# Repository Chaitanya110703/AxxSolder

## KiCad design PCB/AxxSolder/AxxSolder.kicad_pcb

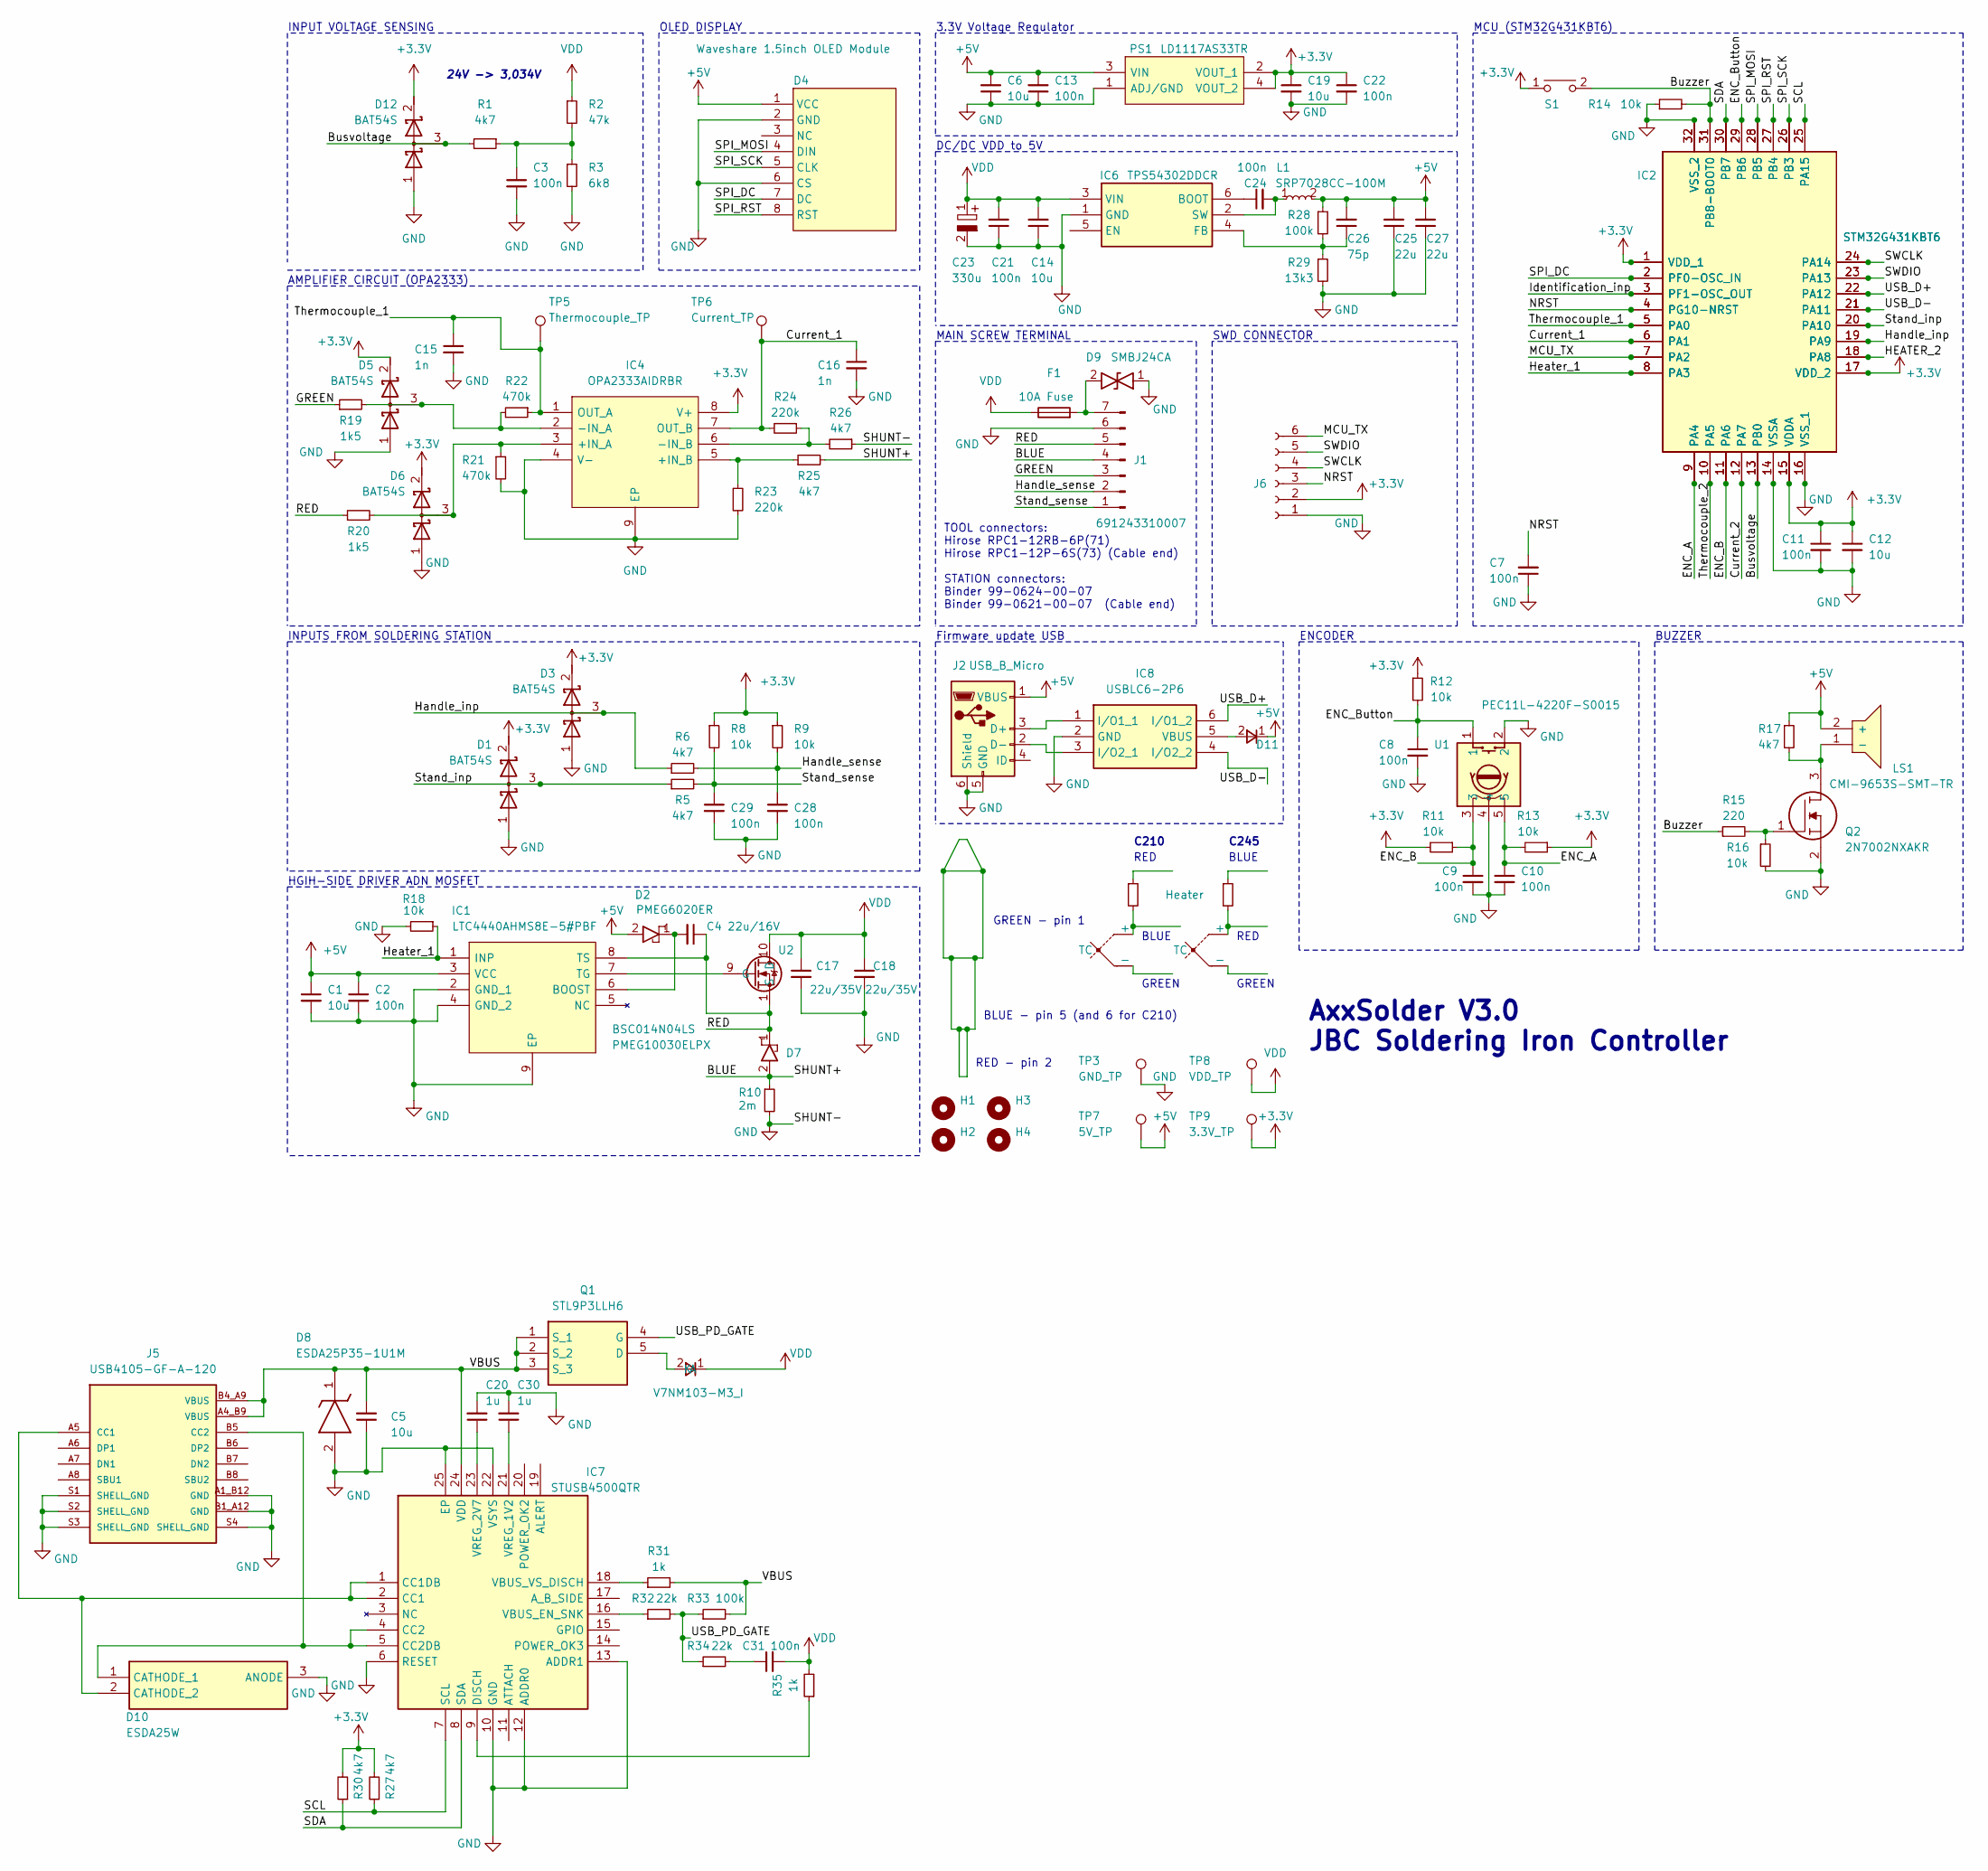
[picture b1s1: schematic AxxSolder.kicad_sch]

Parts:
C1, C5, C6, C12, C14, C19: 10u; C_0805_2012Metric
C2, C3, C7, C8, C9, C10, C11, C13, C21, C22, C24, C28, C29, C31: 100n; C_0805_2012Metric
C4: 22u/16V; C_1206_3216Metric
C15, C16: 1n; C_0805_2012Metric
C17, C18: 22u/35V; C_1206_3216Metric
C20, C30: 1u; C_0805_2012Metric
C23: 330u; CAPAE1030X1050N; Mouser Part Number 661-EMZR500ARA331MJA
C25, C27: 22u; C_1206_3216Metric
C26: 75p; C_0805_2012Metric
D1, D3, D5, D6, D12: BAT54S; SOT95P230X110-3N
D2: PMEG6020ER; PMEG6020ER115; Mouser Part Number 771-PMEG6020ER-115
D4: Waveshare 1.5inch OLED Module; 1_5inch-rgb-oled-module_asm-1110
D7: PMEG10030ELPX; SODFL4725X110N; Mouser Part Number 771-PMEG10030ELPX
D8: ESDA25P35-1U1M; ESDA25P351U1M; Mouser Part Number 511-ESDA25P35-1U1M
D9: SMBJ24CA; DIOM5436X261N; Mouser Part Number 576-SMBJ24CA
D10: ESDA25W; SOT65P210X110-3N; Mouser Part Number 511-ESDA25W
D11: 1N5819HW-7-F; SOD3716X145N; Mouser Part Number 621-1N5819HW-F
D13: V7NM103-M3_I; V7NM103M3I; Mouser Part Number 625-V7NM103-M3/I
F1: 10A Fuse; 3557-2
H1, H2, H3, H4: MountingHole; MountingHole_3mm
IC1: LTC4440AHMS8E-5#PBF; SOP65P490X110-9N; Mouser Part Number 584-C4440AHMS8E-5PBF
IC2: STM32G431KBT6; QFP80P900X900X160-32N; Mouser Part Number 511-STM32G431KBT6
IC4: OPA2333AIDRBR; SON65P300X300X100-9N-D; Mouser Part Number 595-OPA2333AIDRBR
IC5: STM32G431KBT6; UFQFPN-32-1EP_5x5mm_P0.5mm_EP3.5x3.5mm; Mouser Part Number 511-STM32G431KBT6
IC6: TPS54302DDCR; SOT95P280X110-6N; Mouser Part Number 595-TPS54302DDCR
IC7: STUSB4500QTR; QFN50P400X400X100-25N-D; Mouser Part Number 511-STUSB4500QTR
IC8: USBLC6-2P6; USBLC62P6; Mouser Part Number 511-USBLC6-2P6
J1: Conn_01x07_Male; 691243310007; Manufacturer_Part_Number 691243310007
J2: USB_B_Micro; GCT_USB3140-30-0230-1-C_REVE1
J5: USB4105-GF-A-120; GCT_USB4105-GF-A-120; PARTREV A3
J6: Conn_01x06_Socket; PinSocket_1x06_P2.54mm_Vertical
L1: SRP7028CC-100M; INDPM7366X300N; Manufacturer_Part_Number SRP7028CC-100M
LS1: CMI-9653S-SMT-TR; CMI9653SSMTTR; Mouser Part Number 490-CMI-9653S-SMT-TR
PS1: LD1117AS33TR; SOT230P700X190-4N; Mouser Part Number 511-LD1117AS33
Q1: STL9P3LLH6; STL20N6F7; Mouser Part Number 511-STL9P3LLH6
Q2: 2N7002NXAKR; SOT95P230X110-3N; Manufacturer_Part_Number 2N7002NXAKR; Mouser Part Number 771-2N7002NXAKR
R1, R5, R6, R17, R25, R26, R27, R30: 4k7; R_0805_2012Metric
R2: 47k; R_0805_2012Metric
R3: 6k8; R_0805_2012Metric
R4: Heater
R7: Heater 2 OHM
R8, R9, R11, R12, R13, R14, R16, R18: 10k; R_0805_2012Metric
R10: 2m; RESC6432X89N; part_id WSLP25122L500FEA
R15: 220; R_0805_2012Metric
R19, R20: 1k5; R_0805_2012Metric
R21, R22: 470k; R_0805_2012Metric
R23, R24: 220k; R_0805_2012Metric
R28, R33: 100k; R_0805_2012Metric
R29: 13k3; R_0805_2012Metric
R31, R35: 1k; R_0805_2012Metric
R32, R34: 22k; R_0805_2012Metric
S1: PTS636_SM43_SMTR_LFS; PTS636SM43SMTRLFS; Mouser Part Number 611-PTS636SM43SMTRLF
TC1, TC2: TC
TP3: GND_TP; TestPoint_THTPad_D1.0mm_Drill0.5mm
TP5: Thermocouple_TP; TestPoint_Pad_D1.0mm
TP6: Current_TP; TestPoint_Pad_D1.0mm
TP7: 5V_TP; TestPoint_THTPad_D1.0mm_Drill0.5mm
TP8: VDD_TP; TestPoint_THTPad_D1.0mm_Drill0.5mm
TP9: 3.3V_TP; TestPoint_THTPad_D1.0mm_Drill0.5mm
U1: PEC11L-4220F-S0015; PEC11L4220FS0015; Mouser Part Number 652-PEC11L4220FS0015
U2: BSC014N04LS

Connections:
+3.3V: C11.1, C12.1, C19.1, C22.1, D1.2 (K), D3.2 (K), D5.2 (K), D6.2 (K), D12.2 (K), IC2.1 (VDD_1), IC2.15 (VDDA), IC2.17 (VDD_2), IC4.8 (V+), IC5.1 (VDD_1), IC5.15 (VDDA), IC5.17 (VDD_2), J6.2, PS1.2 (VOUT_1), PS1.4 (VOUT_2), R8.1, R9.1, R11.2, R12.1, R13.1, R27.2, R30.2, S1.1, TP9.1
+5V: C1.1, C2.1, C6.2, C13.2, C25.2, C26.2, C27.2, D2.2, D4.1 (VCC), D11.1, IC1.3 (VCC), J2.1 (VBUS), L1.2, LS1.2 (+), PS1.3 (VIN), R17.1, R28.1, TP7.1
/BLUE: D7.2, J1.4, R10.1, R25.2
/Busvoltage: D12.3 (common), IC2.13 (PB0), IC5.13 (PB0), R1.2
/Buzzer: IC2.31 (PB8-BOOT0), IC5.31 (PB8-BOOT0), R14.2, R15.1, S1.2
/Current_1: C16.1, IC2.6 (PA1), IC4.7 (OUT_B), IC5.6 (PA1), R24.2, TP6.1
/Current_2: IC2.12 (PA7), IC5.12 (PA7)
/ENC_A: C10.1, IC2.9 (PA4), IC5.9 (PA4), R13.2, U1.5
/ENC_B: C9.1, IC2.11 (PA6), IC5.11 (PA6), R11.1, U1.3
/ENC_Button: C8.1, IC2.29 (PB6), IC5.29 (PB6), R12.2, U1.1
/GREEN: J1.3, R19.1
/HEATER_2: IC2.18 (PA8), IC5.18 (PA8)
/Handle_inp: D3.3 (common), IC2.19 (PA9), IC5.19 (PA9), R6.1
/Handle_sense: C28.1, J1.2, R6.2, R9.2
/Heater_1: IC1.1 (INP), IC2.8 (PA3), IC5.8 (PA3), R18.1
/Identification_inp: IC2.3 (PF1-OSC_OUT), IC5.3 (PF1-OSC_OUT)
/MCU_TX: IC2.7 (PA2), IC5.7 (PA2), J6.6
/NRST: C7.2, IC2.4 (PG10-NRST), IC5.4 (PG10-NRST), J6.3
/RED: C4.1, D7.1, IC1.8 (TS), J1.5, R20.1, U2.1 (S)
/SCL: IC2.25 (PA15), IC5.25 (PA15), IC7.7 (SCL), R27.1
/SDA: IC2.30 (PB7), IC5.30 (PB7), IC7.8 (SDA), R30.1
/SPI_DC: D4.7 (DC), IC2.2 (PF0-OSC_IN), IC5.2 (PF0-OSC_IN)
/SPI_MOSI: D4.4 (DIN), IC2.28 (PB5), IC5.28 (PB5)
/SPI_RST: D4.8 (RST), IC2.27 (PB4), IC5.27 (PB4)
/SPI_SCK: D4.5 (CLK), IC2.26 (PB3), IC5.26 (PB3)
/SWCLK: IC2.24 (PA14), IC5.24 (PA14), J6.4
/SWDIO: IC2.23 (PA13), IC5.23 (PA13), J6.5
/Stand_inp: D1.3 (common), IC2.20 (PA10), IC5.20 (PA10), R5.1
/Stand_sense: C29.1, J1.1, R5.2, R8.2
/Thermocouple_1: C15.1, IC2.5 (PA0), IC4.1 (OUT_A), IC5.5 (PA0), R22.1, TP5.1
/Thermocouple_2: IC2.10 (PA5), IC5.10 (PA5)
/USB_D+: IC2.22 (PA12), IC5.22 (PA12), IC8.6 (I/O1_2)
/USB_D-: IC2.21 (PA11), IC5.21 (PA11), IC8.4 (I/O2_2)
/USB_PD_GATE: Q1.4 (G), R32.2, R33.1, R34.1
/VBUS: C5.2, D8.1 (K), IC7.24 (VDD), J5.A4_B9 (VBUS), J5.B4_A9 (VBUS), Q1.1 (S_1), Q1.2 (S_2), Q1.3 (S_3), R31.2, R33.2
GND: C1.2, C2.2, C3.2, C5.1, C6.1, C7.1, C8.2, C9.2, C10.2, C11.2, C12.2, C13.1, C14.1, C15.2, C16.2, C17.2, C18.2, C19.2, C20.2, C21.1, C22.2, C23.2, C25.1, C27.1, C28.2, C29.2, C30.2, D1.1 (A), D3.1 (A), D4.2 (GND), D4.6 (CS), D5.1 (A), D6.1 (A), D8.2 (A), D9.1, D10.3 (ANODE), D12.1 (A), IC1.2 (GND_1), IC1.4 (GND_2), IC1.9 (EP), IC2.14 (VSSA), IC2.16 (VSS_1), IC2.32 (VSS_2), IC4.4 (V-), IC4.9 (EP), IC5.14 (VSSA), IC5.16 (VSS_1), IC5.32 (VSS_2), IC6.1 (GND), IC7.6 (RESET), IC7.10 (GND), IC7.12 (ADDR0), IC7.13 (ADDR1), IC7.22 (VSYS), IC7.25 (EP), IC8.2 (GND), J1.6, J2.5 (GND), J2.6 (Shield), J5.A1_B12 (GND), J5.B1_A12 (GND), J5.S1 (SHELL_GND), J5.S2 (SHELL_GND), J5.S3 (SHELL_GND), J5.S4 (SHELL_GND), J6.1, PS1.1 (ADJ/GND), Q2.2, R3.2, R10.2, R14.1, R16.2, R18.2, R21.2, R23.2, R26.1, R29.2, TP3.1, U1.2, U1.4
unnamed: C3.1, R1.1, R2.2, R3.1
unnamed: C31.1, R34.2
unnamed: D5.3 (common), IC4.2 (-IN_A), R19.2, R22.2
unnamed: D6.3 (common), IC4.3 (+IN_A), R20.2, R21.1
unnamed: D10.1 (CATHODE_1), IC7.4 (CC2), IC7.5 (CC2DB), J5.B5 (CC2)
unnamed: D10.2 (CATHODE_2), IC7.1 (CC1DB), IC7.2 (CC1), J5.A5 (CC1)
unnamed: D13.2 (A), Q1.5 (D)
unnamed: C4.2, D2.1, IC1.6 (BOOST)
unnamed: IC1.7 (TG), U2.9 (G)
unnamed: IC4.5 (+IN_B), R23.1, R25.1
unnamed: IC4.6 (-IN_B), R24.1, R26.2
unnamed: C24.1, IC6.6 (BOOT)
unnamed: C26.1, IC6.4 (FB), R28.2, R29.1
unnamed: C24.2, IC6.2 (SW), L1.1
unnamed: IC7.9 (DISCH), R35.1
unnamed: IC7.16 (VBUS_EN_SNK), R32.1
unnamed: IC7.18 (VBUS_VS_DISCH), R31.1
unnamed: C30.1, IC7.21 (VREG_1V2)
unnamed: C20.1, IC7.23 (VREG_2V7)
unnamed: IC8.1 (I/O1_1), J2.3 (D+)
unnamed: IC8.3 (I/O2_1), J2.2 (D-)
unnamed: D11.2, IC8.5 (VBUS)
unnamed: D9.2, F1.2, J1.7
unnamed: LS1.1 (-), Q2.3, R17.2
unnamed: Q2.1, R15.2, R16.1
unnamed: R4.2, TC1.1 (+)
unnamed: R7.2, TC2.1 (+)
VDD: C14.2, C17.1, C18.1, C21.2, C23.1, C31.2, D13.1 (K), F1.1, IC6.3 (VIN), R2.1, R35.2, TP8.1, U2.10 (D)

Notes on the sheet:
C210
Firmware update USB
MCU (STM32G431KBT6)
C245
GREEN - pin 1
MAIN SCREW TERMINAL
AMPLIFIER CIRCUIT (OPA2333)
24V -> 3,034V
INPUT VOLTAGE SENSING
ENCODER
SWD CONNECTOR
BLUE
BLUE - pin 5 (and 6 for C210)
GREEN
RED
BUZZER
DC/DC VDD to 5V
AxxSolder V3.0 JBC Soldering Iron Controller
TOOL connectors: Hirose RPC1-12RB-6P(71) Hirose RPC1-12P-6S(73) (Cable end) STATION connectors: Binder 99-0624-00-07 Binder 99-0621-00-07 (Cable end)
INPUTS FROM SOLDERING STATION
HGIH-SIDE DRIVER ADN MOSFET
RED - pin 2
RED
3.3V Voltage Regulator
OLED DISPLAY

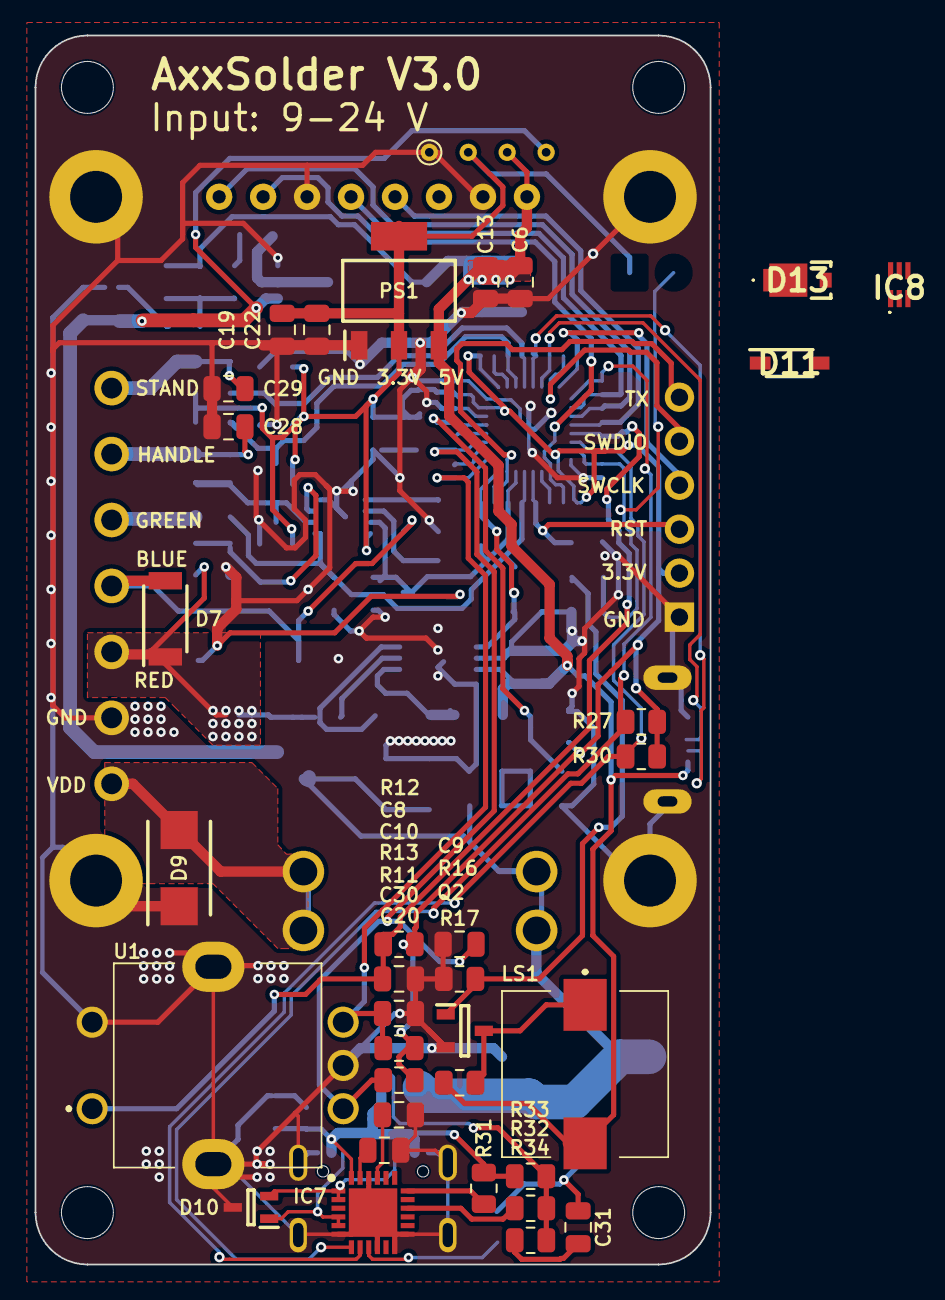
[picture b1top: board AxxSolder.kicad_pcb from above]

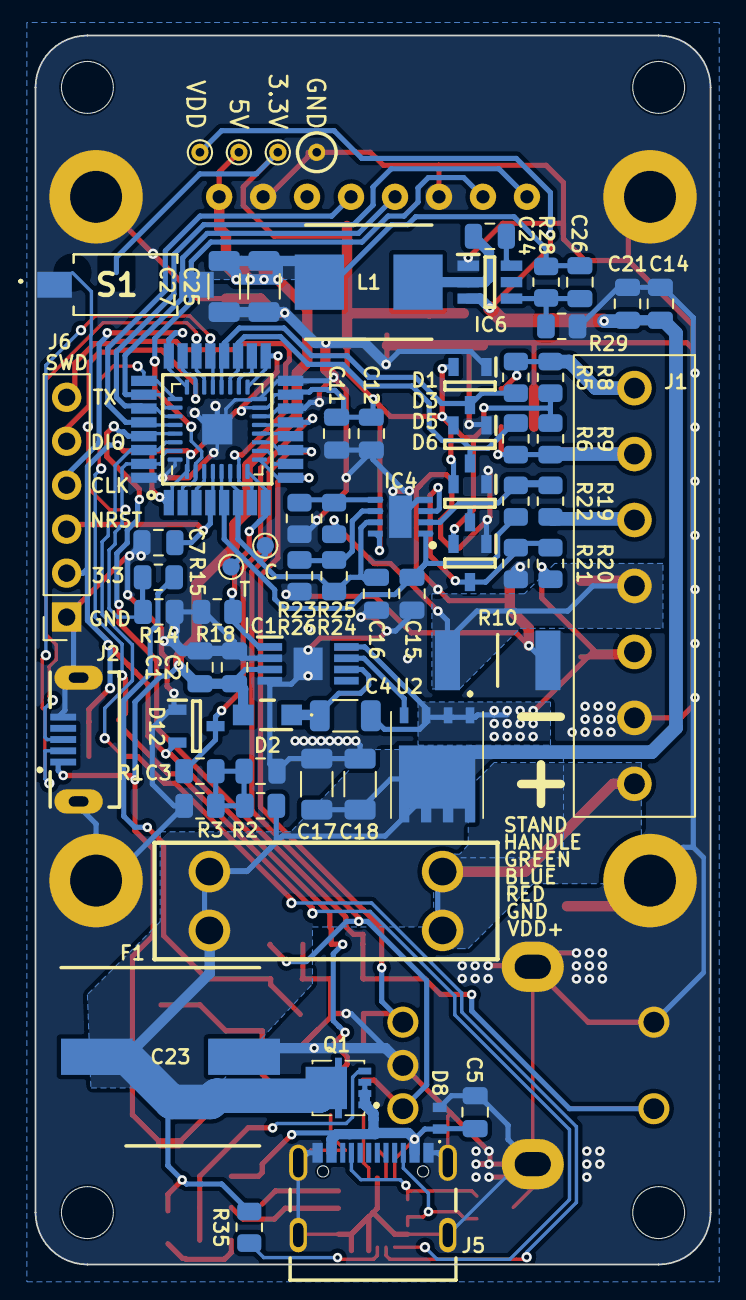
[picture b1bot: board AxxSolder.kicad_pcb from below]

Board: 2 copper layers, 39.0 x 71.0 mm, 107 parts (68 on the bottom side), 62 nets.

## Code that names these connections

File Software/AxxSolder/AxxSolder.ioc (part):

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Mcu.Name=STM32G431K(6-8-B)Tx
Mcu.Package=LQFP32
Mcu.UserName=STM32G431KBTx
PA0.GPIOParameters=GPIO_Label
PA0.GPIO_Label=THERMOCOUPLE_1
PA0.Mode=IN1-Single-Ended
PA0.Signal=ADC1_IN1
PA1.GPIOParameters=GPIO_Label
PA1.GPIO_Label=CURRENT_1
PA1.Mode=IN2-Single-Ended
PA1.Signal=ADC1_IN2
PA10.GPIOParameters=GPIO_Label
PA10.GPIO_Label=STAND_INP
PA10.Signal=GPIO_Input
PA11.Mode=Device
PA11.Signal=USB_DM
PA12.Mode=Device
PA12.Signal=USB_DP
PA13.GPIOParameters=GPIO_Label
PA13.GPIO_Label=T_SWDIO
PA13.Mode=Serial_Wire
PA13.Signal=SYS_JTMS-SWDIO
PA14.GPIOParameters=GPIO_Label
PA14.GPIO_Label=T_SWCLK
PA14.Mode=Serial_Wire
PA14.Signal=SYS_JTCK-SWCLK
PA15.Mode=I2C
PA15.Signal=I2C1_SCL
PA2.Mode=Half_duplex(single_wire_mode)
PA2.Signal=USART2_TX
PA3.GPIOParameters=GPIO_Label
PA3.GPIO_Label=HEATER_1
PA3.Signal=S_TIM2_CH4
PA4.Signal=S_TIM3_CH2
PA5.GPIOParameters=GPIO_Label
PA5.GPIO_Label=THERMOCOUPLE_2
PA5.Mode=IN13-Single-Ended
PA5.Signal=ADC2_IN13
PA6.Signal=S_TIM3_CH1
PA7.GPIOParameters=GPIO_Label
PA7.GPIO_Label=CURRENT_2
PA7.Mode=IN4-Single-Ended
PA7.Signal=ADC2_IN4
PA8.GPIOParameters=GPIO_Label
PA8.GPIO_Label=HEATER_2
PA8.Signal=S_TIM1_CH1
PA9.GPIOParameters=GPIO_Label
PA9.GPIO_Label=HANDLE_INP
PA9.Signal=GPIO_Input
PB0.GPIOParameters=GPIO_Label
PB0.GPIO_Label=BUSVOLTAGE
PB0.Mode=IN15-Single-Ended
PB0.Signal=ADC1_IN15
PB3.Mode=TX_Only_Simplex_Unidirect_Master
PB3.Signal=SPI1_SCK
PB4.GPIOParameters=GPIO_PuPd,GPIO_Label
PB4.GPIO_Label=SPI_RST
PB4.GPIO_PuPd=GPIO_NOPULL
PB4.Signal=GPIO_Output
PB5.Mode=TX_Only_Simplex_Unidirect_Master
PB5.Signal=SPI1_MOSI
PB6.GPIOParameters=GPIO_Label
PB6.GPIO_Label=ENC_BUTTON
PB6.Signal=GPXTI6
PB7.Mode=I2C
PB7.Signal=I2C1_SDA
PB8-BOOT0.GPIOParameters=GPIO_Label
PB8-BOOT0.GPIO_Label=BUZZER
PB8-BOOT0.Signal=S_TIM8_CH2
PF0-OSC_IN.GPIOParameters=GPIO_Label
PF0-OSC_IN.GPIO_Label=SPI_DC
PF0-OSC_IN.Signal=GPIO_Output
PF1-OSC_OUT.GPIOParameters=GPIO_Label
PF1-OSC_OUT.GPIO_Label=IDENTIFICATION_INP
PF1-OSC_OUT.Mode=IN10-Single-Ended
PF1-OSC_OUT.Signal=ADC2_IN10
RCC.HSE_VALUE=8000000
RCC.SYSCLKFreq_VALUE=170000000
RCC.SYSCLKSource=RCC_SYSCLKSOURCE_PLLCLK
board=NUCLEO-G431KB
boardIOC=true

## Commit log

2023-10-12 add flash.c and flash.h and implement flash read/write into main
2023-10-12 Implement Flash read/write and CRC
2023-10-15 Add new libraries for USBC PD
2023-10-20 add libraries and import components for USB firmware upload and USB PD
2023-10-21 update for USB support
2023-10-22 Update to PCB
